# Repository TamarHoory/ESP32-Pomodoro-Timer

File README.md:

# ESP32 Pomodoro Timer ⏱️

A standalone, tactile desktop Pomodoro productivity timer powered by an **ESP32** microcontroller and a **16x2 I2C LCD (LCD1602)** display. Complete with custom KiCad hardware schematics, (PCB layout currently in progress), and robust, non-blocking Arduino/PlatformIO firmware.

---

## 🌟 Highlights

- **Microcontroller**: ESP32 (ESP32-WROOM-32 / ESP32 DevKit)
- **Display**: 16x2 Character LCD via I2C backpack (PCF8574) with auto-address discovery (`0x27` / `0x3F`) and real-time visual progress bar.
- **Tactile Push Buttons**:
  - **Start / Pause**: Toggle countdown or resume paused sessions.
  - **Reset**: Instantly reset session to the configured interval.
  - **Set Time**: Cycle duration in 5-minute steps (5 min up to 60 min).
- **Audio Feedback**: Piezo buzzer delivers audible clicks on button press and a celebratory victory fanfare when the timer completes.
- **Robust Firmware**:
  - Clean **Finite State Machine (FSM)**: `IDLE`, `RUNNING`, `PAUSED`, and `COMPLETED`.
  - Fully **non-blocking timekeeping** using `millis()`.
  - Software debouncing (50 ms) utilizing internal ESP32 pull-ups (`INPUT_PULLUP`).
  - Flicker-free LCD updates (no full-screen clears during ticks).
- **Hardware Ready**: Includes complete **KiCad** electrical schematics (`.kicad_sch`) and printed circuit board design (`.kicad_pcb`).

---

## 📁 Repository Structure

```text
ESP32-Pomodoro-Timer/
├── Hardware/                          # KiCad electronics design files
│   ├── ESP32 Pomodoro Timer.kicad_sch # Schematic diagram
│   ├── ESP32 Pomodoro Timer.kicad_pcb # PCB routing and layout
│   └── ESP32 Pomodoro Timer.kicad_pro # KiCad project configuration
│
├── ESP32 Pomodoro Timer/              # PlatformIO embedded firmware
│   ├── include/                       # Header declarations
│   ├── lib/                           # Third-party libraries
│   │   └── LiquidCrystal_I2C/         # I2C LCD control library
│   ├── src/
│   │   └── main.cpp                   # Core application logic & state machine
│   ├── test/                          # Unit tests
│   └── platformio.ini                 # PlatformIO environment configuration
│
├── .gitignore                         # Build and temporary files exclusion
├── diagram.json                       # Wokwi simulation diagram
├── wokwi.toml                         # Wokwi simulation configuration
└── README.md                          # Project documentation
```

---

## 🔌 Hardware Pinout & Wiring

| Component | Pin / Terminal | ESP32 GPIO | Description |
|---|---|---|---|
| **LCD1602 (I2C Backpack)** | `SDA` | `GPIO 21` | I2C Data Line (50 kHz clock rate) |
| | `SCL` | `GPIO 22` | I2C Clock Line |
| | `VCC` | `VIN` / `5V` | Module power supply & backlight |
| | `GND` | `GND` | Common ground |
| **Start / Pause Button** | Pin 1 / Switch | `GPIO 18` | Active-LOW (Internal `INPUT_PULLUP`) |
| | Pin 2 / Switch | `GND` | Ground connection |
| **Reset Button** | Pin 1 / Switch | `GPIO 19` | Active-LOW (Internal `INPUT_PULLUP`) |
| | Pin 2 / Switch | `GND` | Ground connection |
| **Set Time Button** | Pin 1 / Switch | `GPIO 23` | Active-LOW (Internal `INPUT_PULLUP`) |
| | Pin 2 / Switch | `GND` | Ground connection |
| **Piezo Buzzer** | Positive (+) | `GPIO 25` | PWM tone signal |
| | Negative (-) | `GND` | Ground connection |

> **Note on LCD Power**: Most LCD1602 I2C backpacks require 5V (`VIN`) for bright backlight and optimal character contrast. The I2C data lines (`SDA`/`SCL`) operate smoothly at 3.3V logic levels on the ESP32.

---

## 🖥️ Display UI & State Machine

The firmware implements a responsive, non-blocking finite state machine displayed across 2 rows of 16 characters:

### 1. Ready / Idle State (`STATE_IDLE`)
Allows setting the session duration using the **Set Time** button:
```text
+----------------+
|[READY]  Set:25m|
|Time:    25:00  |
+----------------+
```

### 2. Focus / Running State (`STATE_RUNNING`)
Active countdown with elapsed ratio visual progress bar:
```text
+----------------+
|FOCUS TIME...   |
|24:12 [===   ]  |
+----------------+
```

### 3. Paused State (`STATE_PAUSED`)
Temporarily pauses countdown without losing elapsed progress:
```text
+----------------+
|[PAUSED]        |
|Time:    18:45  |
+----------------+
```

### 4. Completed State (`STATE_COMPLETED`)
Fires when the timer reaches zero, accompanied by a triple-beep audio chime:
```text
+----------------+
|*** TIME'S UP **|
|GREAT JOB!   :D |
+----------------+
```

---

## 🚀 Getting Started

### Prerequisites

- [VS Code](https://code.visualstudio.com/) with the [PlatformIO IDE extension](https://platformio.org/) installed, OR [PlatformIO Core (CLI)](https://docs.platformio.org/en/latest/core/index.html).
- [KiCad](https://www.kicad.org/) (version 8 or newer) to open and inspect the PCB and schematic.
- A standard micro-USB or USB-C cable to connect the ESP32 to your PC.

### Flashing the Firmware

1. **Clone the repository**:
   ```bash
   git clone https://github.com/TamarHoory/ESP32-Pomodoro-Timer.git
   cd ESP32-Pomodoro-Timer
   ```

2. **Open in VS Code**:
   - Open VS Code.
   - Go to **File > Open Folder...** and select the `ESP32 Pomodoro Timer` folder (or the root workspace).

3. **Build & Upload**:
   - Click the PlatformIO **Build** (✓) icon in the bottom status bar, or run:
     ```bash
     pio run
     ```
   - Connect your ESP32 board and click **Upload** (→), or run:
     ```bash
     pio run --target upload
     ```
     
4. **Monitor Serial Output**:
   - Open the serial monitor at 115200 baud:
     ```bash
     pio device monitor
     ```
  ### Running via Wokwi Simulation:
  You can test and run this project without physical hardware using the [Wokwi simulator](https://wokwi.com/):
      
      1. Make sure you have the **Wokwi Simulator** extension installed in VS Code.
      2. Open the project folder in VS Code.
      3. Open the `diagram.json` file, and click the **Play** button (or use the command palette `Wokwi: Start Simulator`) to run the interactive simulation with the virtual ESP32, LCD, and buttons.
---

## 🛠️ Hardware Fabrication (KiCad)

The `Hardware/` folder contains native KiCad files:
- **`ESP32 Pomodoro Timer.kicad_sch`**: Electrical schematic connecting the ESP32 Dev board, tactile buttons, buzzer, and I2C connector header.
- **`ESP32 Pomodoro Timer.kicad_pcb`**: 2-layer PCB layout with traces, component placements, and mounting holes.

To export Gerber files for PCB manufacturing (JLCPCB, PCBWay, etc.):
1. Open `ESP32 Pomodoro Timer.kicad_pro` in KiCad.
2. In the PCB editor, navigate to **File > Fabrication Outputs > Gerbers (.gbr)**.
3. Generate drill files via **File > Fabrication Outputs > Drill Files (.drl)**.
4. Compress the output directory into a `.zip` archive for ordering.

---

## 👤 Author

**Tamar Hoory**  
- GitHub: [@TamarHoory](https://github.com/TamarHoory)

---

## 📜 License

This project is open-source and available under the [MIT License](LICENSE).

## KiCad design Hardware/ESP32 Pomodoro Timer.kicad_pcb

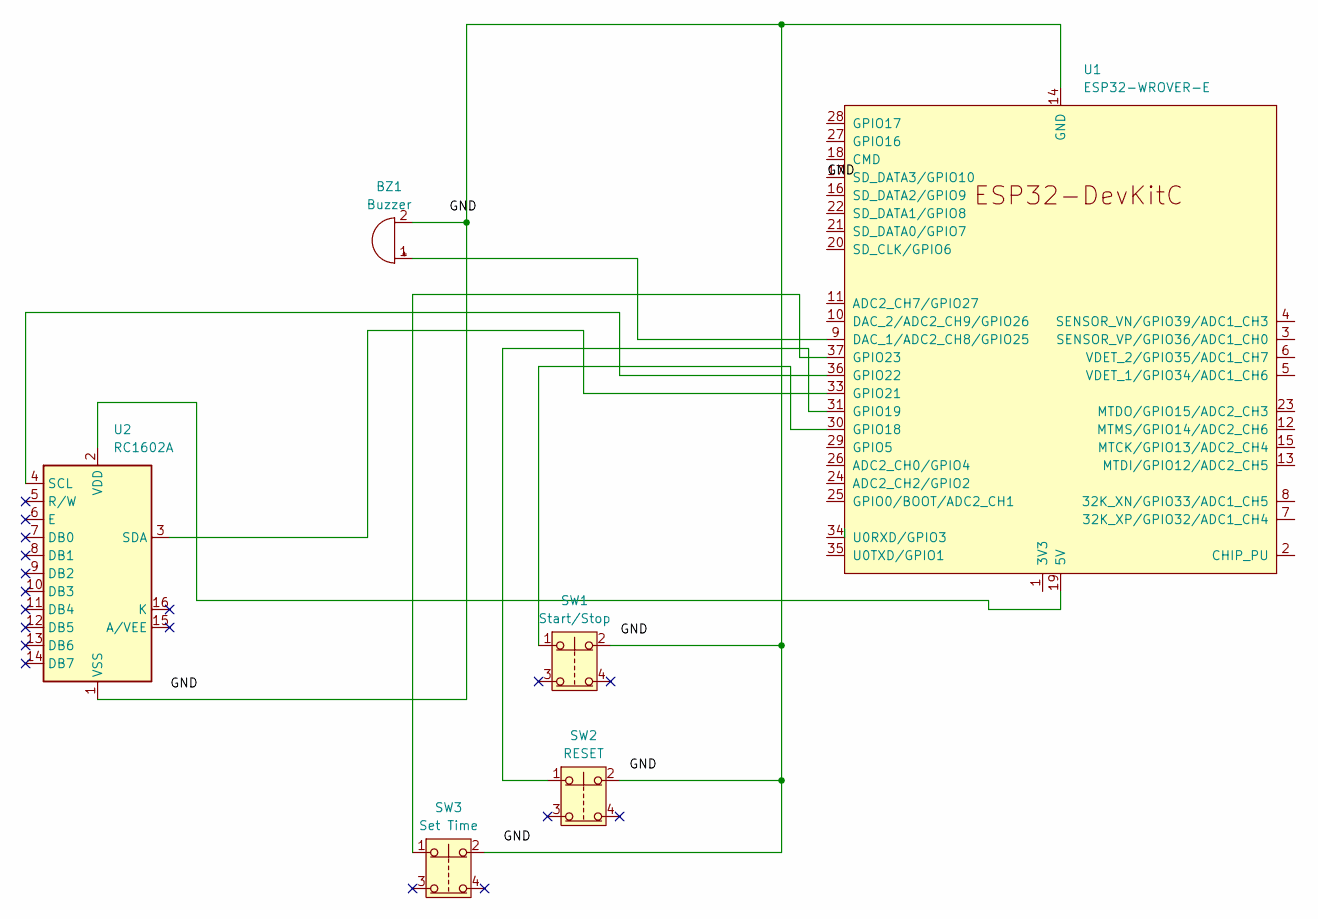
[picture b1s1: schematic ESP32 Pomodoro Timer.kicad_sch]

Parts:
BZ1: Buzzer; Buzzer_12x9.5RM7.6
SW1: Start/Stop; SW_PUSH_6mm_H4.3mm
SW2: RESET; SW_PUSH_6mm_H4.3mm
SW3: Set Time; SW_PUSH_6mm_H4.3mm
U1: ESP32-WROVER-E; ESP32-DevKitC
U2: RC1602A

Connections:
/GND: U1.17 (SD_DATA3/GPIO10)
unnamed: BZ1.1 (+), U1.9 (DAC_1/ADC2_CH8/GPIO25)
unnamed: BZ1.2 (-), SW1.2, SW2.2, SW3.2, U1.14 (GND), U1.32 (GND), U1.38 (GND), U2.1 (VSS)
unnamed: U1.19 (5V), U2.2 (VDD)
unnamed: SW1.1, U1.30 (GPIO18)
unnamed: SW2.1, U1.31 (GPIO19)
unnamed: U1.33 (GPIO21), U2.3 (SDA)
unnamed: U1.36 (GPIO22), U2.4 (SCL)
unnamed: SW3.1, U1.37 (GPIO23)

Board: 2 copper layers, 6 parts (0 on the bottom side), 8 nets, no tracks yet.
